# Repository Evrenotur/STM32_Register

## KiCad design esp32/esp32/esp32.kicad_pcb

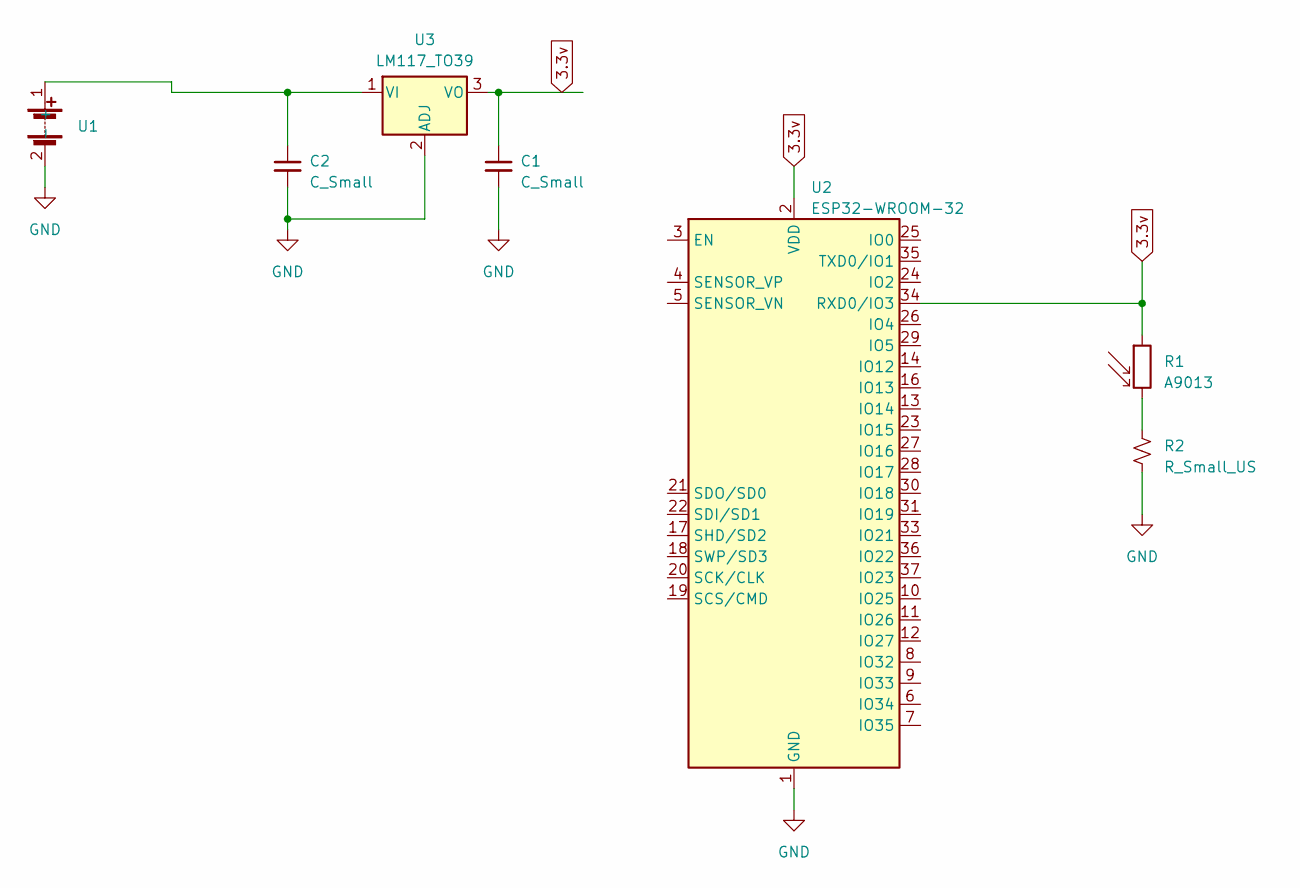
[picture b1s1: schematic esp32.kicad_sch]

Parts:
C1, C2: C_Small; R_0805_2012Metric_Pad1.20x1.40mm_HandSolder
R1: A9013; R_LDR_5.0x4.1mm_P3mm_Vertical
R2: R_Small_US; R_0805_2012Metric_Pad1.20x1.40mm_HandSolder
U1: 9v
U2: ESP32-WROOM-32
U3: LM117_TO39; TO-39-3

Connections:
5v: C1.1, R1.1, U2.2 (VDD), U2.34 (RXD0/IO3), U3.3 (VO)
GND: C1.2, C2.2, R2.1, U1.2 (-), U2.1 (GND), U2.15 (GND), U2.38 (GND), U2.39 (GND), U3.2 (ADJ)
unnamed: R1.2, R2.2
unnamed: C2.1, U1.1 (+), U3.1 (VI)

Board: 2 copper layers, 7 parts (0 on the bottom side), 4 nets, no tracks yet.

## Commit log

2022-07-02 001_SYSTEM_CLOCK_CONFIG_AND_PLL
2022-07-02 002_REGISTER_LED_BLINK
2022-07-04 003_REGISTER_BUTTON_CONTROL
2022-07-04 004_REGISTER_EXTERNAL_INTERRUPT
2022-07-05 005_REGISTER_ADC
2022-07-10 006_REGISTER_DAC
2022-07-10 007_TIMER_REGISTER
2022-07-12 008_PWM_REGISTER
    Üzerinde Çalışılacak
2022-07-14 009_DMA_REGISTER
    Devam Edilecek
2022-07-15 010_USART_REGISTER
2022-09-09 001_REGISTER_CLOCK_CONFIGURATION
2022-09-10 002_REGISTER_GPIO_WRITE
2022-09-10 003_REGISTER_GPIO_READ
2022-09-10 004_REGISTER_GPIO_INTERRUPT
2022-09-16 STM32_Register_32F407G-DISK
2022-10-07 angle_value
2022-10-09 Dynamic
2022-10-27 driver
2022-11-27 servo_control_stm32
2022-11-27 BMP180_STM32Lib
2022-11-28 NEO-6M-GPS
2022-11-28 ESP32
2022-12-20 step_control
2022-12-20 dc_motor_position_control
2022-12-21 deneme
2023-01-27 i2c_oled_example
2023-01-29 lm35
2023-01-29 temp
2023-03-12 Eprom
2023-04-04 Circuit
2023-09-23 modbus
2024-05-12 distance
2024-09-15 UAVCAN
2024-09-16 UAVCAN_F103_2
